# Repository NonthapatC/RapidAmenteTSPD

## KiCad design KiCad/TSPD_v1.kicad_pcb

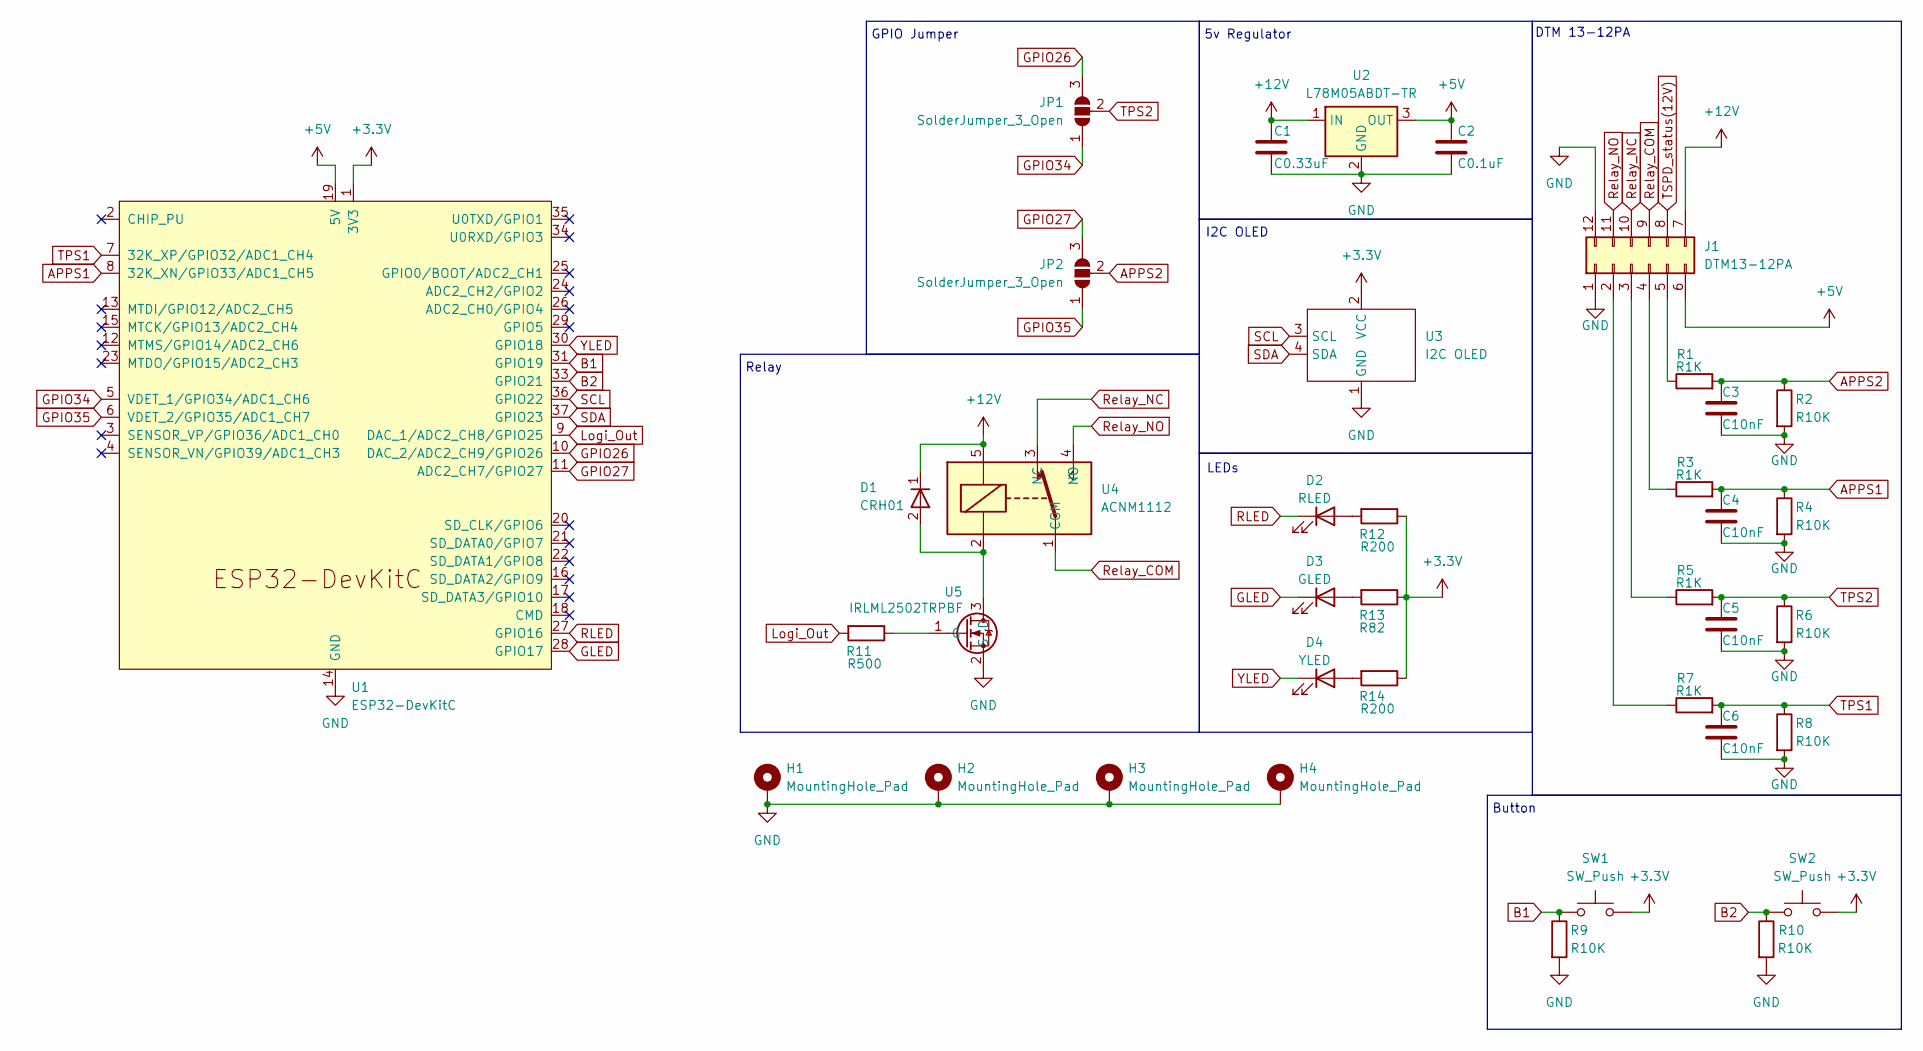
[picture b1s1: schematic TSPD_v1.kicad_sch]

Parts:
C1: C0.33uF; C_0805_2012Metric_Pad1.18x1.45mm_HandSolder
C2: C0.1uF; C_0805_2012Metric_Pad1.18x1.45mm_HandSolder
C3, C4, C5, C6: C10nF; C_0805_2012Metric_Pad1.18x1.45mm_HandSolder
D1: CRH01; S-FLAT(1.6x3.5)
D2: RLED; LED_0805_2012Metric_Pad1.15x1.40mm_HandSolder
D3: GLED; LED_0805_2012Metric_Pad1.15x1.40mm_HandSolder
D4: YLED; LED_0805_2012Metric_Pad1.15x1.40mm_HandSolder
H1, H2, H3, H4: MountingHole_Pad; MountingHole_3.2mm_M3_Pad_Via
J1: DTM13-12PA
JP1, JP2: SolderJumper_3_Open; SolderJumper-3_P1.3mm_Open_RoundedPad1.0x1.5mm_NumberLabels
R1, R3, R5, R7: R1K; R_0805_2012Metric_Pad1.20x1.40mm_HandSolder
R2, R4, R6, R8, R9, R10: R10K; R_0805_2012Metric_Pad1.20x1.40mm_HandSolder
R11: R500; R_0805_2012Metric_Pad1.20x1.40mm_HandSolder
R12, R14: R200; R_0805_2012Metric_Pad1.20x1.40mm_HandSolder
R13: R82; R_0805_2012Metric_Pad1.20x1.40mm_HandSolder
SW1, SW2: SW_Push; SW_PUSH-12mm
U1: ESP32-DevKitC
U2: L78M05ABDT-TR; TO-252-2
U3: I2C OLED; 0.96'' I2C OLED
U4: ACNM1112; PANASONIC ACNM1112
U5: IRLML2502TRPBF; SOT-23_Handsoldering

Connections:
+3.3V: R12.1, R13.1, R14.1, SW1.2, SW2.2, U1.1 (3V3), U3.2 (VCC)
+5V: C2.1, J1.6, U1.19 (5V), U2.3 (OUT)
+12V: C1.1, D1.1, J1.7, U2.1 (IN), U4.5
APPS1: C4.1, R3.2, R4.1, U1.8 (32K_XN/GPIO33/ADC1_CH5)
APPS2: C3.1, JP2.2 (C), R1.2, R2.1
B1: R9.1, SW1.1, U1.31 (GPIO19)
B2: R10.1, SW2.1, U1.33 (GPIO21)
GLED: D3.1 (K), U1.28 (GPIO17)
GND: C1.2, C2.2, C3.2, C4.2, C5.2, C6.2, H1.1, H2.1, H3.1, H4.1, J1.1, J1.12, R2.2, R4.2, R6.2, R8.2, R9.2, R10.2, U1.14 (GND), U1.32 (GND), U1.38 (GND), U2.2 (GND), U3.1 (GND), U5.2 (S)
GPIO26: JP1.3 (B), U1.10 (DAC_2/ADC2_CH9/GPIO26)
GPIO27: JP2.3 (B), U1.11 (ADC2_CH7/GPIO27)
GPIO34: JP1.1 (A), U1.5 (VDET_1/GPIO34/ADC1_CH6)
GPIO35: JP2.1 (A), U1.6 (VDET_2/GPIO35/ADC1_CH7)
Logi_Out: R11.2, U1.9 (DAC_1/ADC2_CH8/GPIO25)
unnamed: D2.2 (A), R12.2
unnamed: D3.2 (A), R13.2
unnamed: D4.2 (A), R14.2
unnamed: J1.2, R7.1
unnamed: J1.3, R5.1
unnamed: J1.4, R3.1
unnamed: J1.5, R1.1
unnamed: D1.2, U4.2, U5.3 (D)
unnamed: R11.1, U5.1 (G)
RLED: D2.1 (K), U1.27 (GPIO16)
Relay_COM: J1.9, U4.1 (COM)
Relay_NC: J1.10, U4.3 (NC)
Relay_NO: J1.11, U4.4 (NO)
SCL: U1.36 (GPIO22), U3.3 (SCL)
SDA: U1.37 (GPIO23), U3.4 (SDA)
TPS1: C6.1, R7.2, R8.1, U1.7 (32K_XP/GPIO32/ADC1_CH4)
TPS2: C5.1, JP1.2 (C), R5.2, R6.1
TSPD_status(12V): J1.8
YLED: D4.1 (K), U1.30 (GPIO18)

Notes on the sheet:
LEDs
5v Regulator
Button
Relay
DTM 13-12PA
I2C OLED
GPIO Jumper

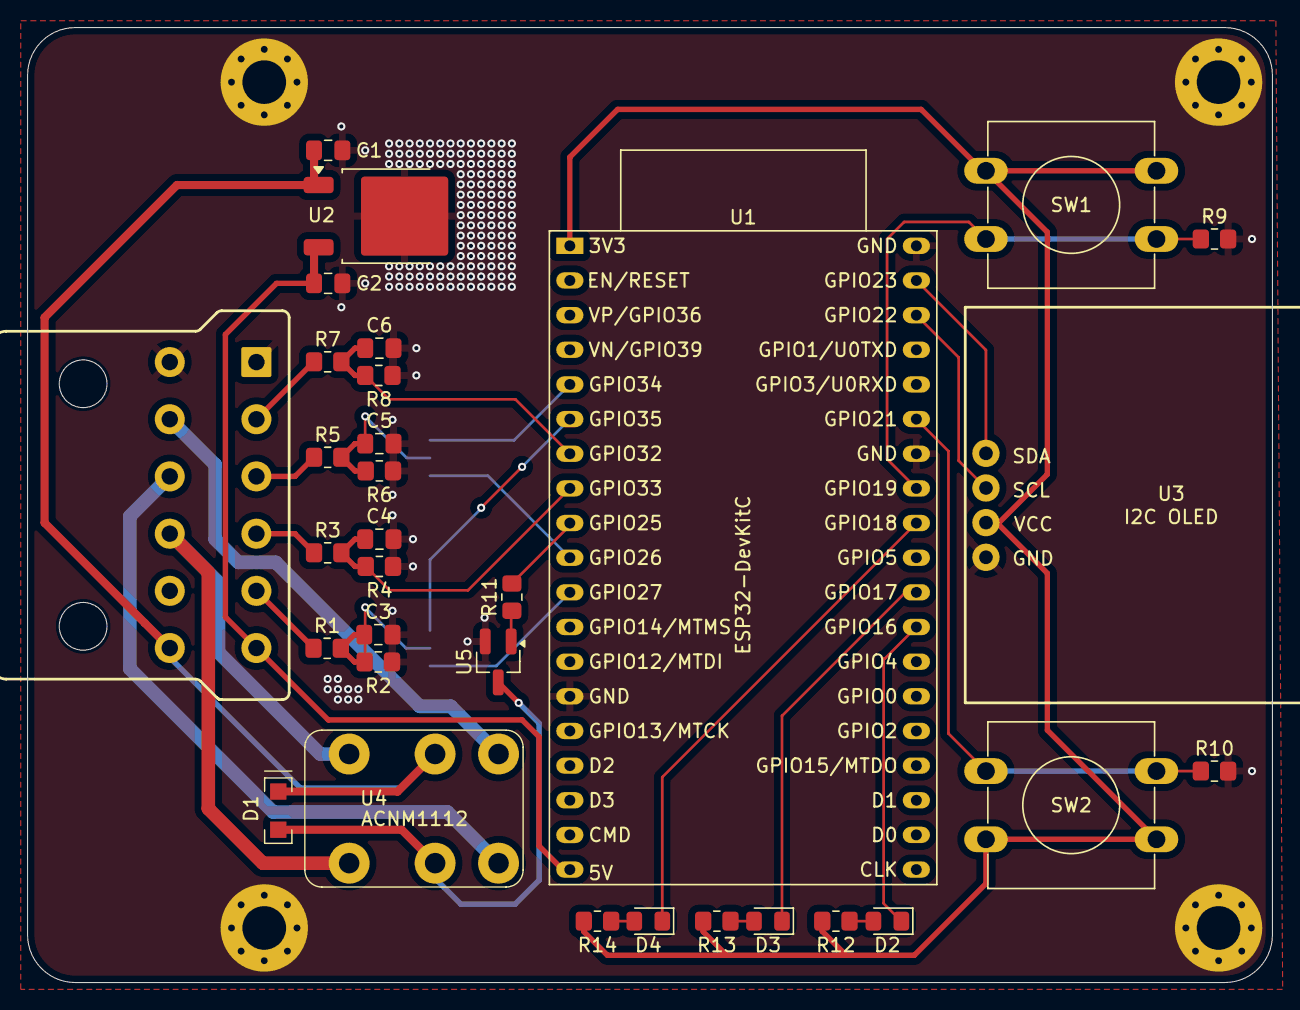
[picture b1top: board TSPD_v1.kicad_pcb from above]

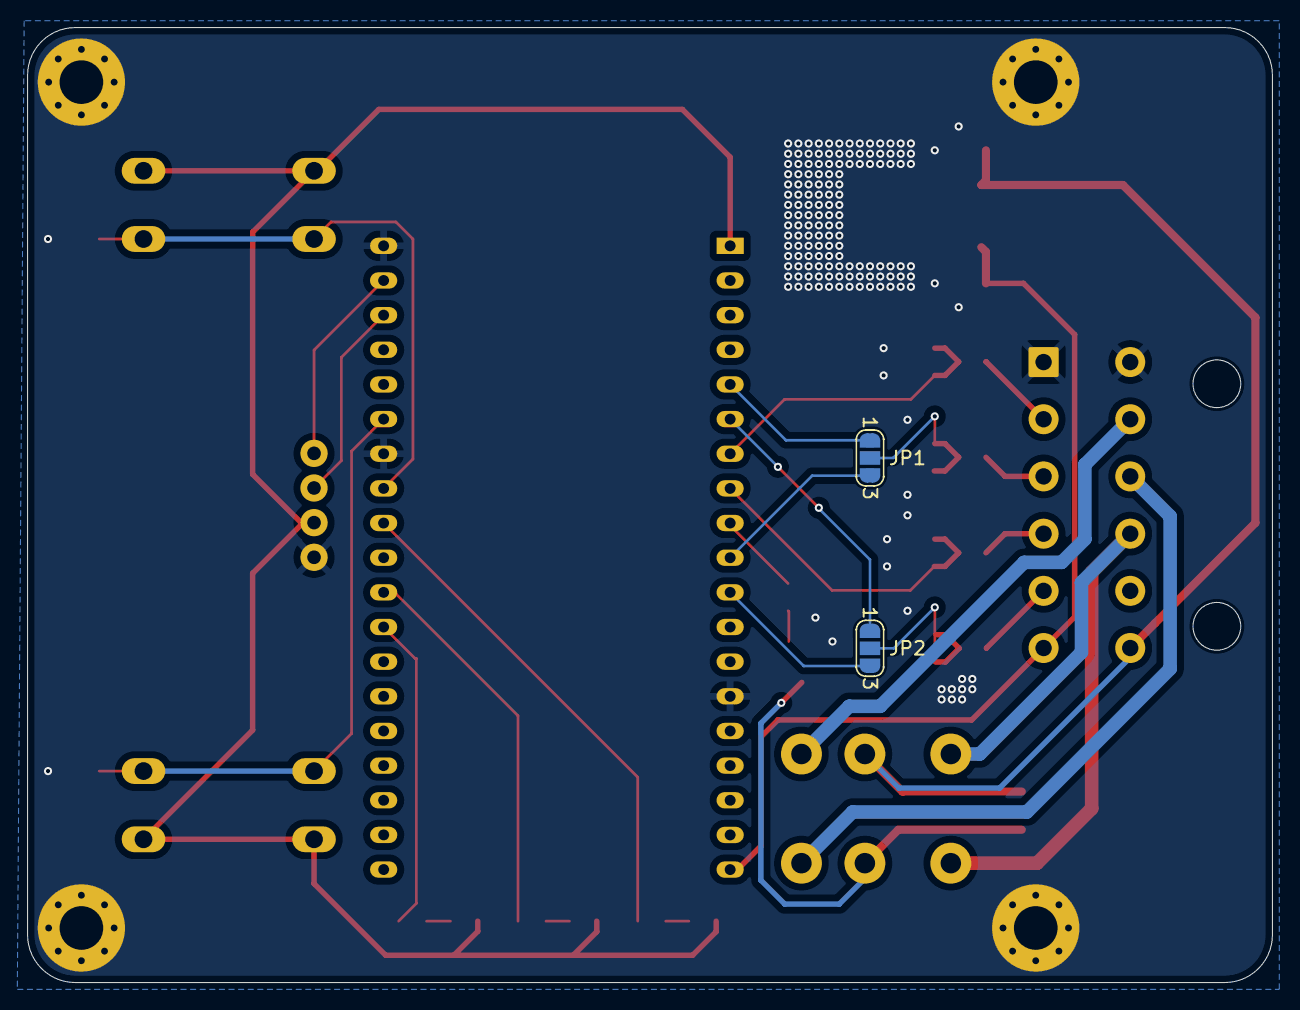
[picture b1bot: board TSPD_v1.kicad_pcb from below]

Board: 2 copper layers, 91.2 x 70.0 mm, 38 parts (2 on the bottom side), 32 nets.

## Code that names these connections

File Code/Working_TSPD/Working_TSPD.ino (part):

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dataPackage calData;

const int PWM_PIN = 27;
const int TPS1_PIN = 34; //TPS1 is actually on pin 32 but switch due to sketchy behavior
//const int TPS2_PIN = 34;

const int RLED = 16;
const int YLED = 18;
const int GLED = 17;

const int button_1 = 19;
const int button_2 = 21;
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    }

    float filteredPWM = PWMduty.update(rawPWM);
    int filteredTPS1 = TPS1.update(analogRead(TPS1_PIN));
    

    Serial.print("Duty: ");
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          float p = measurePWM();
          if(isnan(p)) { i--; continue; }
          PWMduty.update(p);
          TPS1.update(analogRead(TPS1_PIN));
      }
      TPS1sum += filteredTPS1;
      count++;
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  }

  float filteredPWM = PWMduty.update(initialPWM);
  int filteredTPS1 = TPS1.update(analogRead(TPS1_PIN));

  calData.pwmMin = filteredPWM;
  calData.pwmMax = filteredPWM;
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    }
    
    filteredPWM = PWMduty.update(rawPWM);
    filteredTPS1 = TPS1.update(analogRead(TPS1_PIN));

    if(millis() - startTime > calMinMaxTO){
      Serial.println("Min max timed out");
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void setup() {
  Serial.begin(115200);
  pinMode(PWM_PIN, INPUT);
  pinMode(TPS1_PIN, INPUT);

  pinMode(relay, OUTPUT);

  digitalWrite(relay, LOW);

  pinMode(RLED, OUTPUT);
  pinMode(YLED, OUTPUT);
  pinMode(GLED, OUTPUT);

  pinMode(button_1, INPUT);
  pinMode(button_2, INPUT);
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void loop() {
  float rawPWM = measurePWM();
  float filteredPWM = PWMduty.update(rawPWM);
  int rawTPS1 = analogRead(TPS1_PIN);
  int filteredTPS1 = TPS1.update(rawTPS1);

  Serial.print("Duty: ");
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
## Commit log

2026-03-31 MCU code
